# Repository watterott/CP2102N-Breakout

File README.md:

# CP2102N-Breakout
The CP2102N-Breakout is an USB to Serial Adapter with Silicon Labs Chipset.

* [Silabs CP2102N](https://www.silabs.com/products/interface/usb-bridges/usbxpress-usb-bridges/Pages/usbxpress-usb-bridges.aspx) USB UART Bridge (up to 3M baud)
* 3.3V or 5V logic supply voltage selectable by switch
* Rx + Tx Status LEDs
* Overcurrent protection (resettable polyswitch fuse)
* Standard 6 pin connector with GND, CTS, VCC, TX, RX, DTR
* microUSB-Connector
* Open-Source and released under the [Creative Commons Attribution Share-Alike License](https://creativecommons.org/licenses/by-sa/4.0/).
* **[Documentation on learn.watterott.com](https://learn.watterott.com)**

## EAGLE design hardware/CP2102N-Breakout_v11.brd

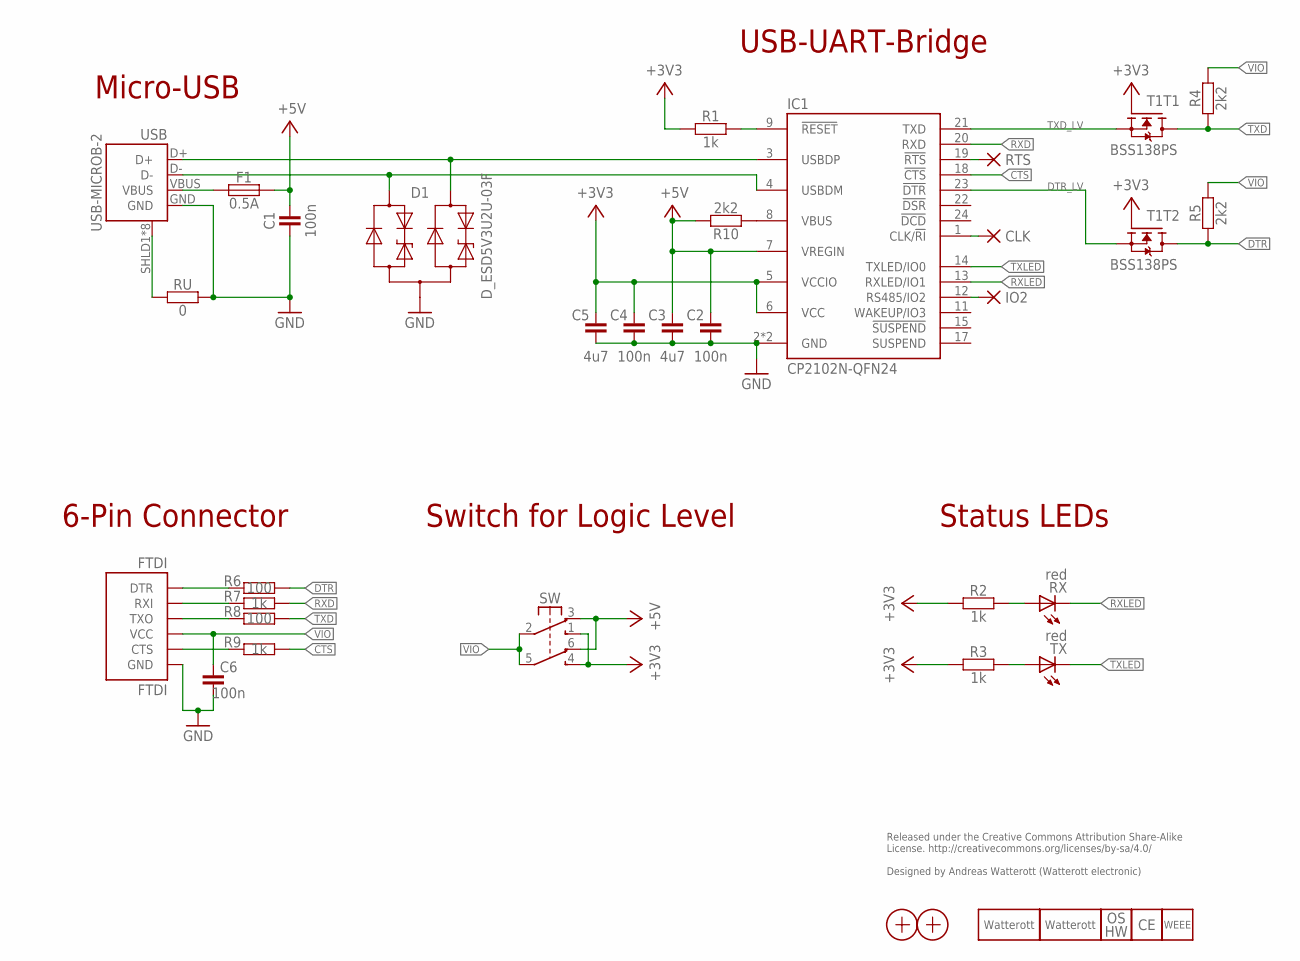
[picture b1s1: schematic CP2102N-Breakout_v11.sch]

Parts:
C1, C2, C4, C6: 100n; C0402
C3, C5: 4u7; C0603
CLK: PAD-0.5_NC
D1: D_ESD5V3U2U-03F; SOT723
F1: 0.5A; C0805
FTDI: FTDI
IC1: CP2102N-QFN24; QFN24-PAD
IO2: PAD-0.5_NC
LOGO5: LOGO_SPARK-2; SPARK_2MM
LOGO6: LOGO_SPARK-4; SPARK_4MM
LOGO7: LOGO_OSHW-2; OSHW_2MM
LOGO8: LOGO_CE-2; CE_2MM
LOGO9: LOGO_WEEE-4; WEEE_4MM
R1, R2, R3, R7, R9: 1k; C0402
R4, R5, R10: 2k2; C0402
R6, R8: 100; C0402
RTS: PAD-0.5_NC
RU: 0; C0402
RX: red; C0603
SW: SW-2UM-CUS22B; CUS22B
T1: BSS138PS; SOT363
TX: red; C0603
USB: USB-MICROB-2; USB-MICROB-10118194
X1, X2: PASSER-07; PASSER_07MM

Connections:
+3V3: C4.2, C5.2, IC1.5 (VCCIO), IC1.6 (VCC), R1.1, R2.1, R3.1, SW.1 (S1), SW.4 (S2), T1.2 (G), T1.5 (G)
+5V: C1.2, C2.2, C3.2, F1.2, IC1.7 (VREGIN), R10.2, SW.3 (O1), SW.6 (O2)
CLK: CLK.1, IC1.1 (CLK/!RI)
CP_VBUS: IC1.8 (VBUS), R10.1
CTS: IC1.18 (!CTS), R9.1
CTSI: FTDI.2-CTS (CTS), R9.2
DTR: R5.1, R6.1, T1.3 (D)
DTRO: FTDI.6-DTR (DTR), R6.2
DTR_LV: IC1.23 (!DTR), T1.4 (S)
D_N: D1.1 (C1), IC1.4 (USBDM), USB.D-
D_P: D1.2 (C2), IC1.3 (USBDP), USB.D+
GND: C1.1, C2.1, C3.1, C4.1, C5.1, C6.1, D1.3 (A), FTDI.1-GND (GND), IC1.2 (GND), IC1.TP (GND), RU.2, USB.GND
IO2: IC1.12 (RS485/IO2), IO2.1
RESET: IC1.9 (!RESET), R1.2
RTS: IC1.19 (!RTS), RTS.1
RX-LED: R2.2, RX.A
RXD: IC1.20 (RXD), R7.1
RXI: FTDI.5-RXI (RXI), R7.2
RXLED: IC1.13 (RXLED/IO1), RX.C
SHLD: RU.1, USB.SHLD1 (SHIELD), USB.SHLD2 (SHIELD), USB.SHLD3 (SHIELD), USB.SHLD4 (SHIELD), USB.SHLD5 (SHIELD), USB.SHLD6 (SHIELD), USB.SHLD7 (SHIELD), USB.SHLD8 (SHIELD)
TX-LED: R3.2, TX.A
TXD: R4.1, R8.1, T1.6 (D)
TXD_LV: IC1.21 (TXD), T1.1 (S)
TXLED: IC1.14 (TXLED/IO0), TX.C
TXO: FTDI.4-TXO (TXO), R8.2
VBUS: F1.1, USB.VBUS
VIO: C6.2, FTDI.3-VCC (VCC), R4.2, R5.2, SW.2 (P1), SW.5 (P2)

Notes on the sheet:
Released under the Creative Commons Attribution Share-Alike License. http://creativecommons.org/licenses/by-sa/4.0/ Designed by Andreas Watterott (Watterott electronic)
USB-UART-Bridge
Micro-USB
6-Pin Connector
Switch for Logic Level
Status LEDs

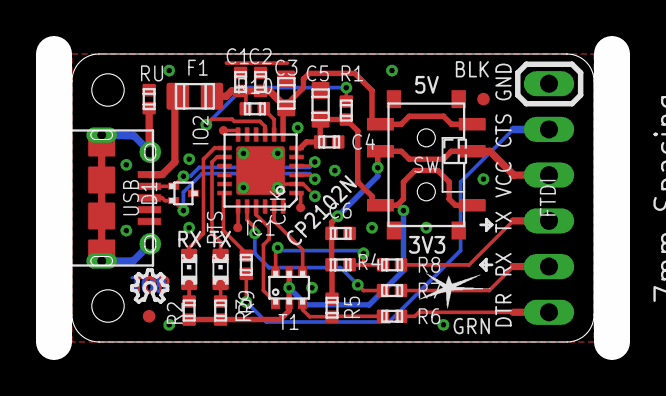
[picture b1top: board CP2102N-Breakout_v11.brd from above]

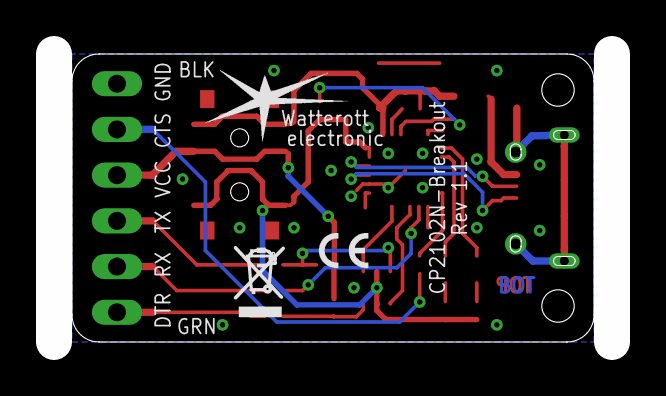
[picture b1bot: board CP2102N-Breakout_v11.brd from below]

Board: 2 copper layers, 31.0 x 16.0 mm, 36 parts (3 on the bottom side), 27 nets.

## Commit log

2018-07-26 added rev 1.1
2018-10-27 updated schematics
2020-10-14 added dimension
